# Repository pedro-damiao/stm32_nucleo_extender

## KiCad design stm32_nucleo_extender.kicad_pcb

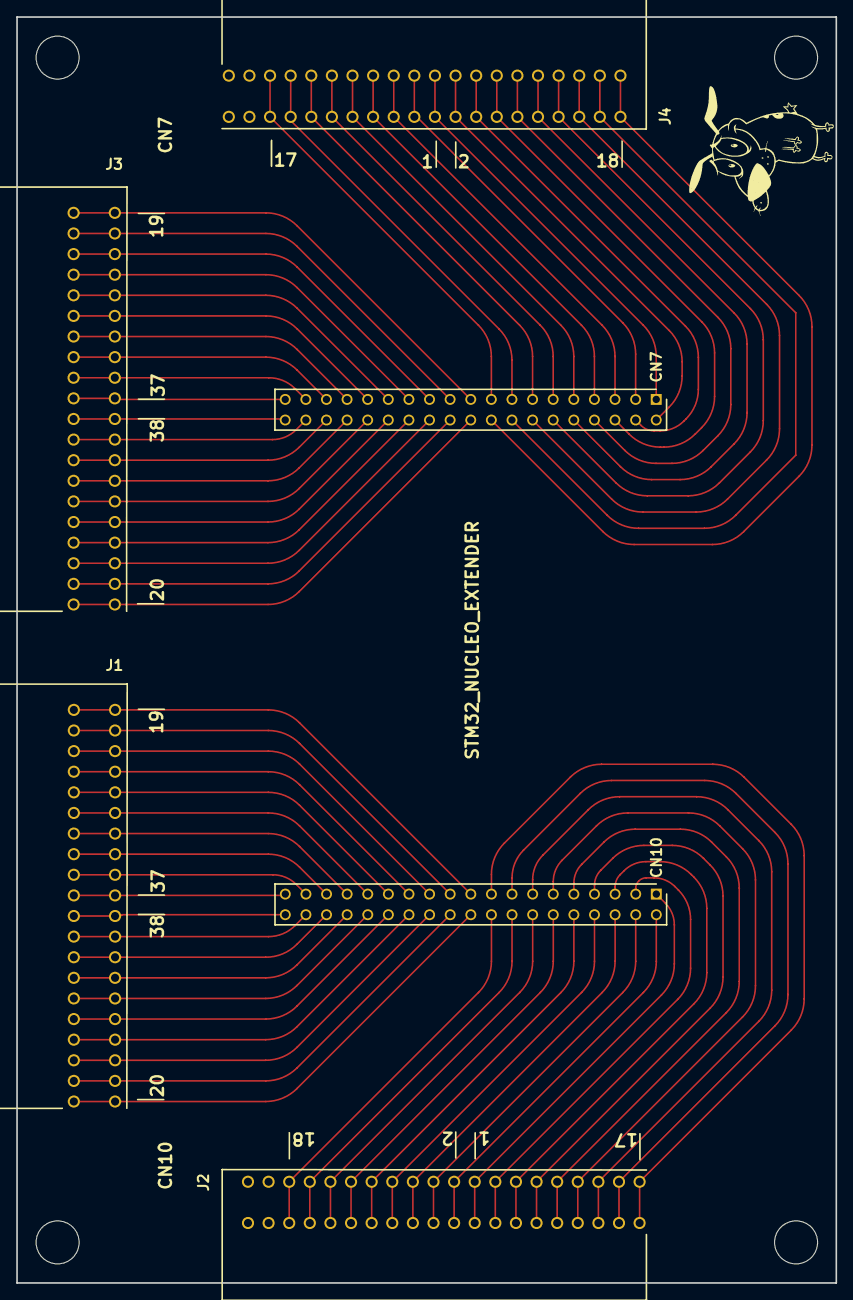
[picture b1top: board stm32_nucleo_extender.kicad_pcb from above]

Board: 2 copper layers, 101.0 x 156.0 mm, 6 parts (0 on the bottom side), 76 nets.

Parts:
CN7, CN10: 6-534206-9; SHDR38W69P254_2X19_4826X503X877P
J1, J2, J3, J4: TBL009-254-20GY-2GY; TBL00925420GY2GY

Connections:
/CN7_1: CN7.1, J4.A10, J4.B10
/CN7_2: CN7.2, J4.A9, J4.B9
/CN7_3: CN7.3, J4.A11, J4.B11
/CN7_4: CN7.4, J4.A8, J4.B8
/CN7_5: CN7.5, J4.A12, J4.B12
/CN7_6: CN7.6, J4.A7, J4.B7
/CN7_7: CN7.7, J4.A13, J4.B13
/CN7_8: CN7.8, J4.A6, J4.B6
/CN7_9: CN7.9, J4.A14, J4.B14
/CN7_10: CN7.10, J4.A5, J4.B5
/CN7_11: CN7.11, J4.A15, J4.B15
/CN7_12: CN7.12, J4.A4, J4.B4
/CN7_13: CN7.13, J4.A16, J4.B16
/CN7_14: CN7.14, J4.A3, J4.B3
/CN7_15: CN7.15, J4.A17, J4.B17
/CN7_16: CN7.16, J4.A2, J4.B2
/CN7_17: CN7.17, J4.A18, J4.B18
/CN7_18: CN7.18, J4.A1, J4.B1
/CN7_19: CN7.19, J3.A1, J3.B1
/CN7_20: CN7.20, J3.A20, J3.B20
/CN7_21: CN7.21, J3.A2, J3.B2
/CN7_22: CN7.22, J3.A19, J3.B19
/CN7_23: CN7.23, J3.A3, J3.B3
/CN7_24: CN7.24, J3.A18, J3.B18
/CN7_25: CN7.25, J3.A4, J3.B4
/CN7_26: CN7.26, J3.A17, J3.B17
/CN7_27: CN7.27, J3.A5, J3.B5
/CN7_28: CN7.28, J3.A16, J3.B16
/CN7_29: CN7.29, J3.A6, J3.B6
/CN7_30: CN7.30, J3.A15, J3.B15
/CN7_31: CN7.31, J3.A7, J3.B7
/CN7_32: CN7.32, J3.A14, J3.B14
/CN7_33: CN7.33, J3.A8, J3.B8
/CN7_34: CN7.34, J3.A13, J3.B13
/CN7_35: CN7.35, J3.A9, J3.B9
/CN7_36: CN7.36, J3.A12, J3.B12
/CN7_37: CN7.37, J3.A10, J3.B10
/CN7_38: CN7.38, J3.A11, J3.B11
/CN10_1: CN10.1, J2.A12, J2.B12
/CN10_2: CN10.2, J2.A11, J2.B11
/CN10_3: CN10.3, J2.A13, J2.B13
/CN10_4: CN10.4, J2.A10, J2.B10
/CN10_5: CN10.5, J2.A14, J2.B14
/CN10_6: CN10.6, J2.A9, J2.B9
/CN10_7: CN10.7, J2.A15, J2.B15
/CN10_8: CN10.8, J2.A8, J2.B8
/CN10_9: CN10.9, J2.A16, J2.B16
/CN10_10: CN10.10, J2.A7, J2.B7
/CN10_11: CN10.11, J2.A17, J2.B17
/CN10_12: CN10.12, J2.A6, J2.B6
/CN10_13: CN10.13, J2.A18, J2.B18
/CN10_14: CN10.14, J2.A5, J2.B5
/CN10_15: CN10.15, J2.A19, J2.B19
/CN10_16: CN10.16, J2.A4, J2.B4
/CN10_17: CN10.17, J2.A20, J2.B20
/CN10_18: CN10.18, J2.A3, J2.B3
/CN10_19: CN10.19, J1.A1, J1.B1
/CN10_20: CN10.20, J1.A20, J1.B20
/CN10_21: CN10.21, J1.A2, J1.B2
/CN10_22: CN10.22, J1.A19, J1.B19
/CN10_23: CN10.23, J1.A3, J1.B3
/CN10_24: CN10.24, J1.A18, J1.B18
/CN10_25: CN10.25, J1.A4, J1.B4
/CN10_26: CN10.26, J1.A17, J1.B17
/CN10_27: CN10.27, J1.A5, J1.B5
/CN10_28: CN10.28, J1.A16, J1.B16
/CN10_29: CN10.29, J1.A6, J1.B6
/CN10_30: CN10.30, J1.A15, J1.B15
/CN10_31: CN10.31, J1.A7, J1.B7
/CN10_32: CN10.32, J1.A14, J1.B14
/CN10_33: CN10.33, J1.A8, J1.B8
/CN10_34: CN10.34, J1.A13, J1.B13
/CN10_35: CN10.35, J1.A9, J1.B9
/CN10_36: CN10.36, J1.A12, J1.B12
/CN10_37: CN10.37, J1.A10, J1.B10
/CN10_38: CN10.38, J1.A11, J1.B11

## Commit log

2026-03-15 Initial KiCad project import
2026-04-23 [UPD] to kicad 10.0 [ADD] round tracks
2026-04-28 [ADD] components to project
2026-04-28 [ADD] jlcpcb needed files
2026-04-28 [ADD] logo and holes
